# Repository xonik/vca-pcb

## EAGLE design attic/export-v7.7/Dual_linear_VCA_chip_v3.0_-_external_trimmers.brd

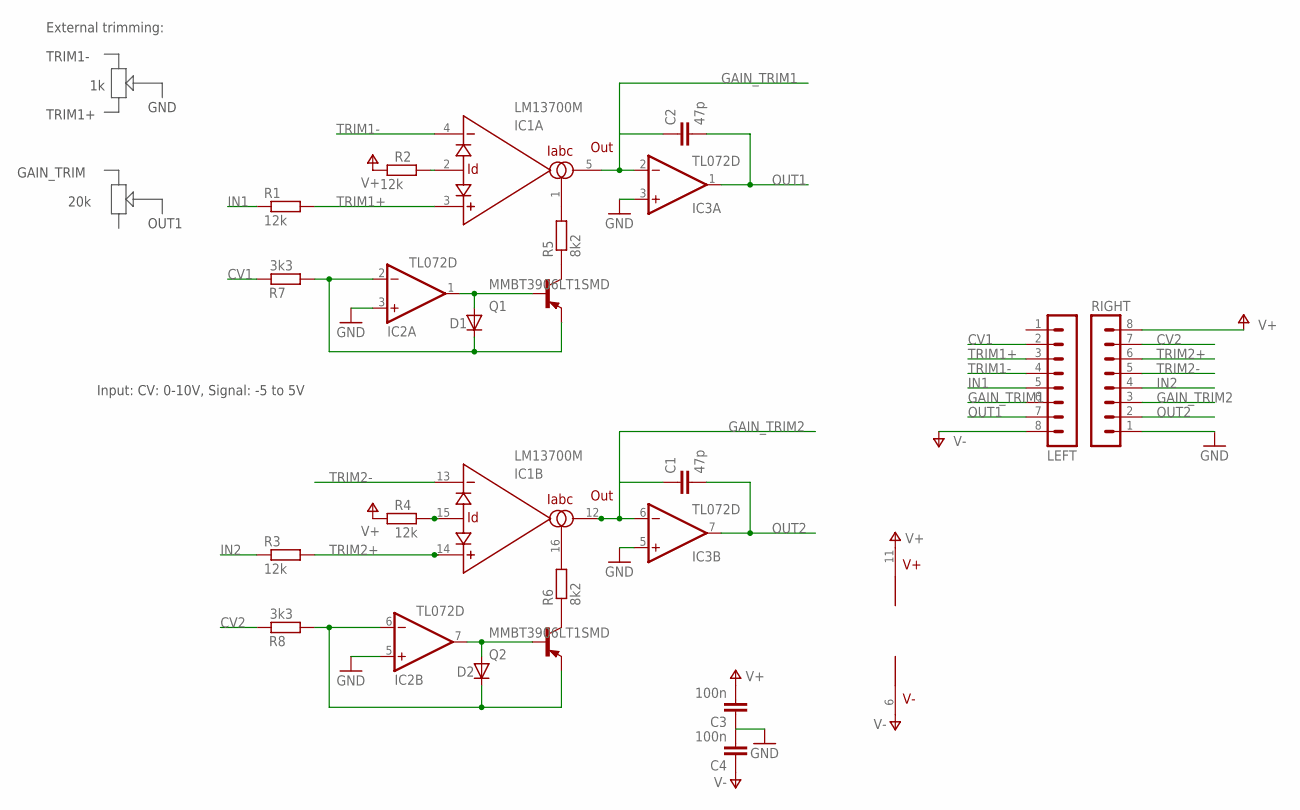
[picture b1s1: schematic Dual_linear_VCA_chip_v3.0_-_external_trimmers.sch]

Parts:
C1, C2: 47p; C0805
C3, C4: 100n; C0805
D1, D2: DIODE-SOD80C; SOD80C
IC1: LM13700M; SO16
IC2, IC3: TL072D; SO08
LEFT: MA08-1JC; MA08-1J
Q1, Q2: MMBT3906LT1SMD; SOT23-BEC
R1, R2, R3, R4: 12k; R0805
R5, R6: 8k2; R0805
R7, R8: 3k3; R0805
RIGHT: MA08-1JC; MA08-1J

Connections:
CV1: LEFT.2, R7.2
CV2: R8.2, RIGHT.7
GAIN_TRIM1: C2.1, IC1.5 (OUT), IC3.2 (-IN), LEFT.6
GAIN_TRIM2: C1.1, IC1.12 (OUT), IC3.6 (-IN), RIGHT.3
GND: C3.1, C4.2, IC2.3 (+IN), IC2.5 (+IN), IC3.3 (+IN), IC3.5 (+IN), RIGHT.1
IN1: LEFT.5, R1.1
IN2: R3.1, RIGHT.4
unnamed: Q1.C, R5.1
unnamed: Q2.C, R6.1
unnamed: D1.C, IC2.2 (-IN), Q1.E, R7.1
unnamed: IC1.1 (IABC), R5.2
unnamed: IC1.2 (ID), R2.2
unnamed: D2.A, IC2.7 (OUT), Q2.B
unnamed: D1.A, IC2.1 (OUT), Q1.B
unnamed: D2.C, IC2.6 (-IN), Q2.E, R8.1
unnamed: IC1.16 (IABC), R6.2
unnamed: IC1.15 (ID), R4.2
OUT1: C2.2, IC3.1 (OUT), LEFT.7
OUT2: C1.2, IC3.7 (OUT), RIGHT.2
TRIM1+: IC1.3 (+IN), LEFT.3, R1.2
TRIM1-: IC1.4 (-IN), LEFT.4
TRIM2+: IC1.14 (+IN), R3.2, RIGHT.6
TRIM2-: IC1.13 (-IN), RIGHT.5
V+: C3.2, IC1.11 (V+), IC2.8 (V+), IC3.8 (V+), R2.1, R4.1, RIGHT.8
V-: C4.1, IC1.6 (V-), IC2.4 (V-), IC3.4 (V-), LEFT.8

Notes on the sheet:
Input: CV: 0-10V, Signal: -5 to 5V
TRIM1-
TRIM1+
GND
External trimming:
GAIN_TRIM
OUT1
20k

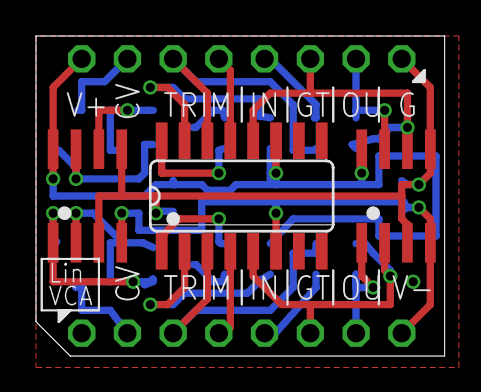
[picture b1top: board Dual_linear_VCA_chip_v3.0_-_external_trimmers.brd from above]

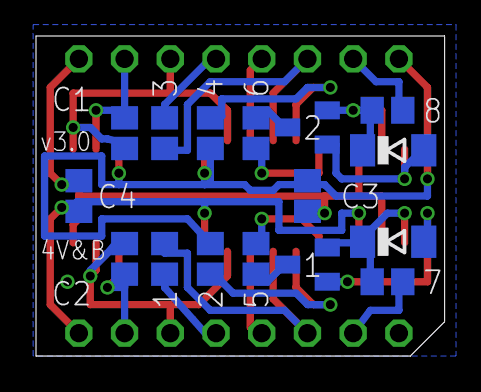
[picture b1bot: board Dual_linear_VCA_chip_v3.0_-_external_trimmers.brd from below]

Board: 2 copper layers, 22.7 x 17.8 mm, 21 parts (16 on the bottom side), 25 nets.

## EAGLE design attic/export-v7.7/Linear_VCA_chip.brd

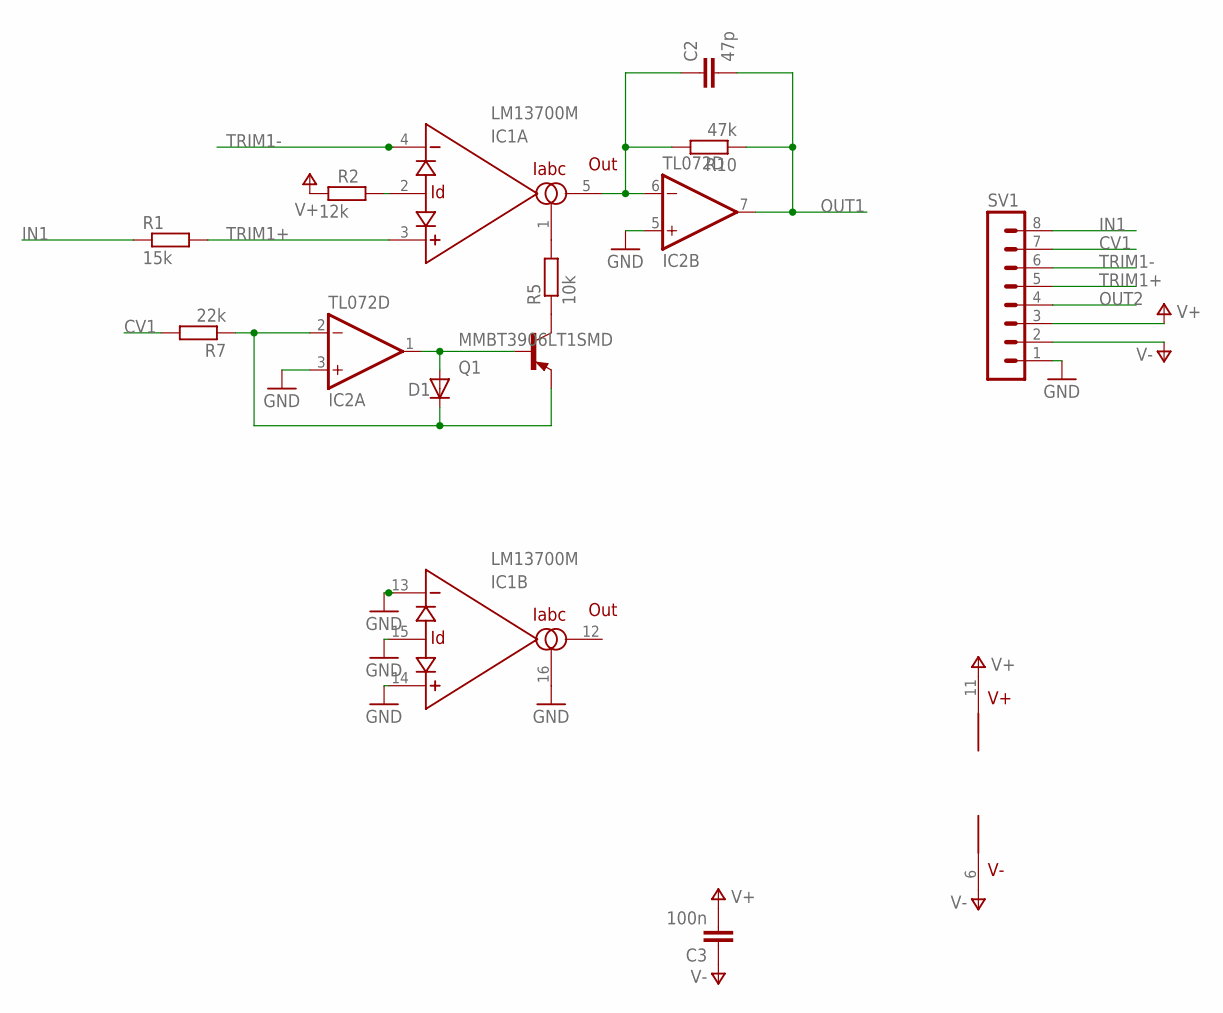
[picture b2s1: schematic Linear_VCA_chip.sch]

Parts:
C2: 47p; C0805
C3: 100n; C0805
D1: DIODE-SOD80C; SOD80C
IC1: LM13700M; SO16
IC2: TL072D; SO08
Q1: MMBT3906LT1SMD; SOT23-BEC
R1: 15k; R0805
R2: 12k; R0805
R5: 10k; R0805
R7: 22k; R0805
R10: 47k; R0805
SV1: MA08-1

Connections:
CV1: R7.2, SV1.7
GND: IC1.13 (-IN), IC1.14 (+IN), IC1.15 (ID), IC1.16 (IABC), IC2.3 (+IN), IC2.5 (+IN), SV1.1
IN1: R1.1, SV1.8
unnamed: Q1.C, R5.1
unnamed: D1.C, IC2.2 (-IN), Q1.E, R7.1
unnamed: IC1.1 (IABC), R5.2
unnamed: IC1.2 (ID), R2.2
unnamed: C2.1, IC1.5 (OUT), IC2.6 (-IN), R10.2
unnamed: D1.A, IC2.1 (OUT), Q1.B
OUT1: C2.2, IC2.7 (OUT), R10.1
OUT2: SV1.4
TRIM1+: IC1.3 (+IN), R1.2, SV1.5
TRIM1-: IC1.4 (-IN), SV1.6
V+: C3.2, IC1.11 (V+), IC2.8 (V+), R2.1, SV1.3
V-: C3.1, IC1.6 (V-), IC2.4 (V-), SV1.2

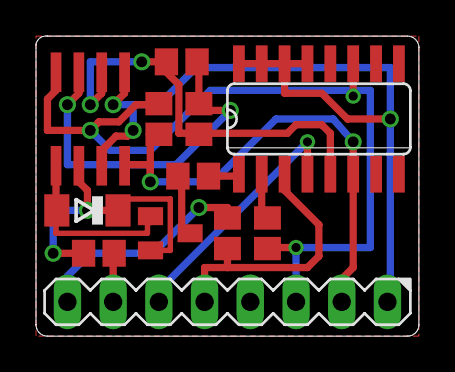
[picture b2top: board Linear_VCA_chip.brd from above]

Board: 2 copper layers, 21.3 x 16.7 mm, 12 parts (0 on the bottom side), 14 nets.

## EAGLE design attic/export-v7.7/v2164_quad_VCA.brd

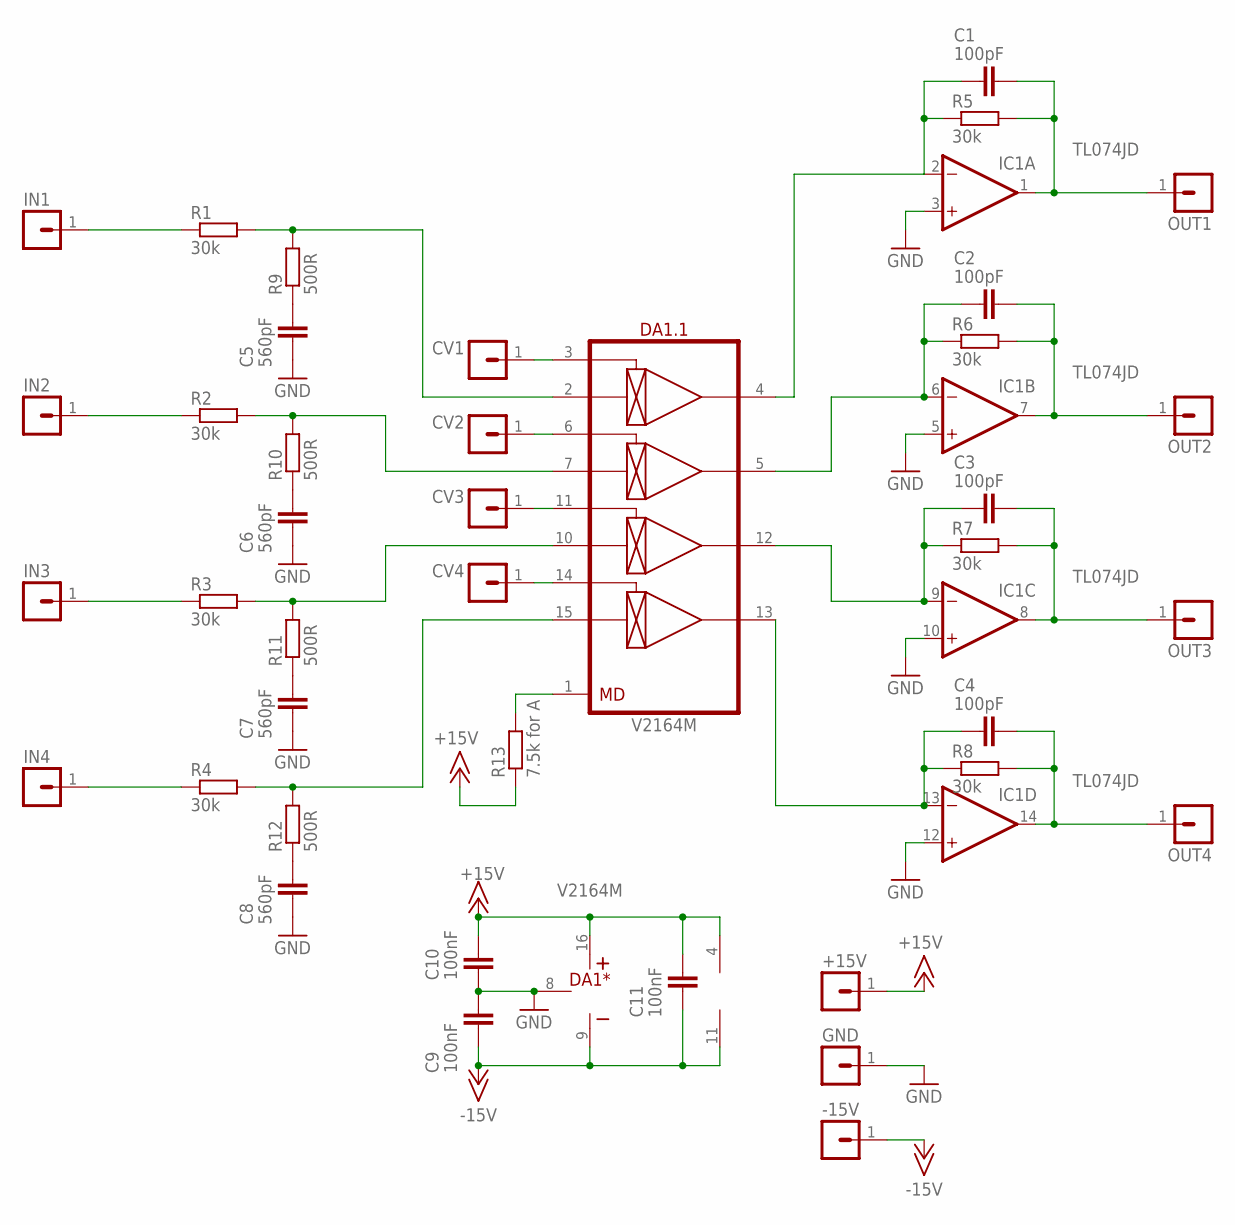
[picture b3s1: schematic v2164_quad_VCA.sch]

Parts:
+15V: MA01-1JN; MA01N-1J
-15V: MA01-1JN; MA01N-1J
C1, C2, C3, C4: 100pF; C0603
C5, C6, C7, C8: 560pF; C0603
C9, C10, C11: 100nF; C0603
CV1, CV2, CV3, CV4: MA01-1JN; MA01N-1J
DA1: V2164M; SO-16
GND: MA01-1JN; MA01N-1J
IC1: TL074JD; SO14J
IN1, IN2, IN3, IN4: MA01-1JN; MA01N-1J
OUT1, OUT2, OUT3, OUT4: MA01-1JN; MA01N-1J
R1, R2, R3, R4, R5, R6, R7, R8: 30k; R0603
R9, R10, R11, R12: 500R; R0603
R13: 7.5k for A; R0603

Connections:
+15V: +15V.1, C10.2, C11.2, DA1.16 (V+), IC1.4 (V+), R13.1
-15V: -15V.1, C9.1, C11.1, DA1.9 (V-), IC1.11 (V-)
CV1: CV1.1, DA1.3 (CV1)
CV2: CV2.1, DA1.6 (CV2)
CV3: CV3.1, DA1.11 (CV3)
CV4: CV4.1, DA1.14 (CV4)
GND: C5.1, C6.1, C7.1, C8.1, C9.2, C10.1, DA1.8 (GND), GND.1, IC1.3 (+IN), IC1.5 (+IN), IC1.10 (+IN), IC1.12 (+IN)
IN1: IN1.1, R1.1
IN2: IN2.1, R2.1
IN3: IN3.1, R3.1
IN4: IN4.1, R4.1
unnamed: C4.1, DA1.13 (OUT4), IC1.13 (-IN), R8.1
unnamed: DA1.1 (MD), R13.2
unnamed: C3.1, DA1.12 (OUT3), IC1.9 (-IN), R7.1
unnamed: C2.1, DA1.5 (OUT2), IC1.6 (-IN), R6.1
unnamed: C1.1, DA1.4 (OUT1), IC1.2 (-IN), R5.1
unnamed: C5.2, R9.1
unnamed: C6.2, R10.1
unnamed: C7.2, R11.1
unnamed: C8.2, R12.1
unnamed: DA1.2 (IN1), R1.2, R9.2
unnamed: DA1.7 (IN2), R2.2, R10.2
unnamed: DA1.10 (IN3), R3.2, R11.2
unnamed: DA1.15 (IN4), R4.2, R12.2
OUT1: C1.2, IC1.1 (OUT), OUT1.1, R5.2
OUT2: C2.2, IC1.7 (OUT), OUT2.1, R6.2
OUT3: C3.2, IC1.8 (OUT), OUT3.1, R7.2
OUT4: C4.2, IC1.14 (OUT), OUT4.1, R8.2

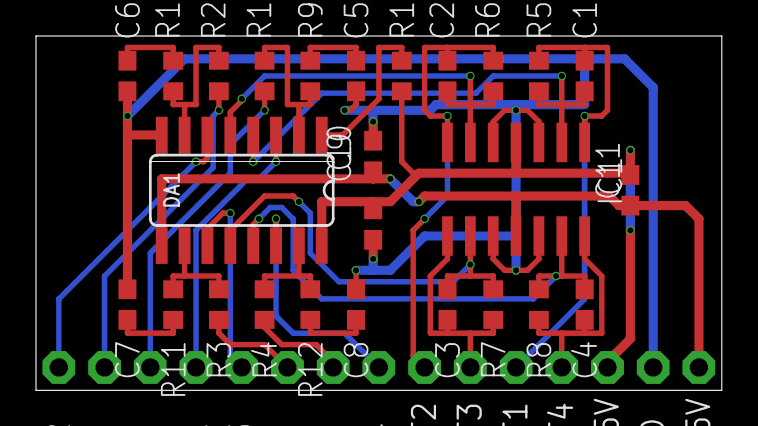
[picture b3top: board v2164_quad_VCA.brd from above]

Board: 2 copper layers, 38.1 x 19.7 mm, 41 parts (0 on the bottom side), 28 nets.

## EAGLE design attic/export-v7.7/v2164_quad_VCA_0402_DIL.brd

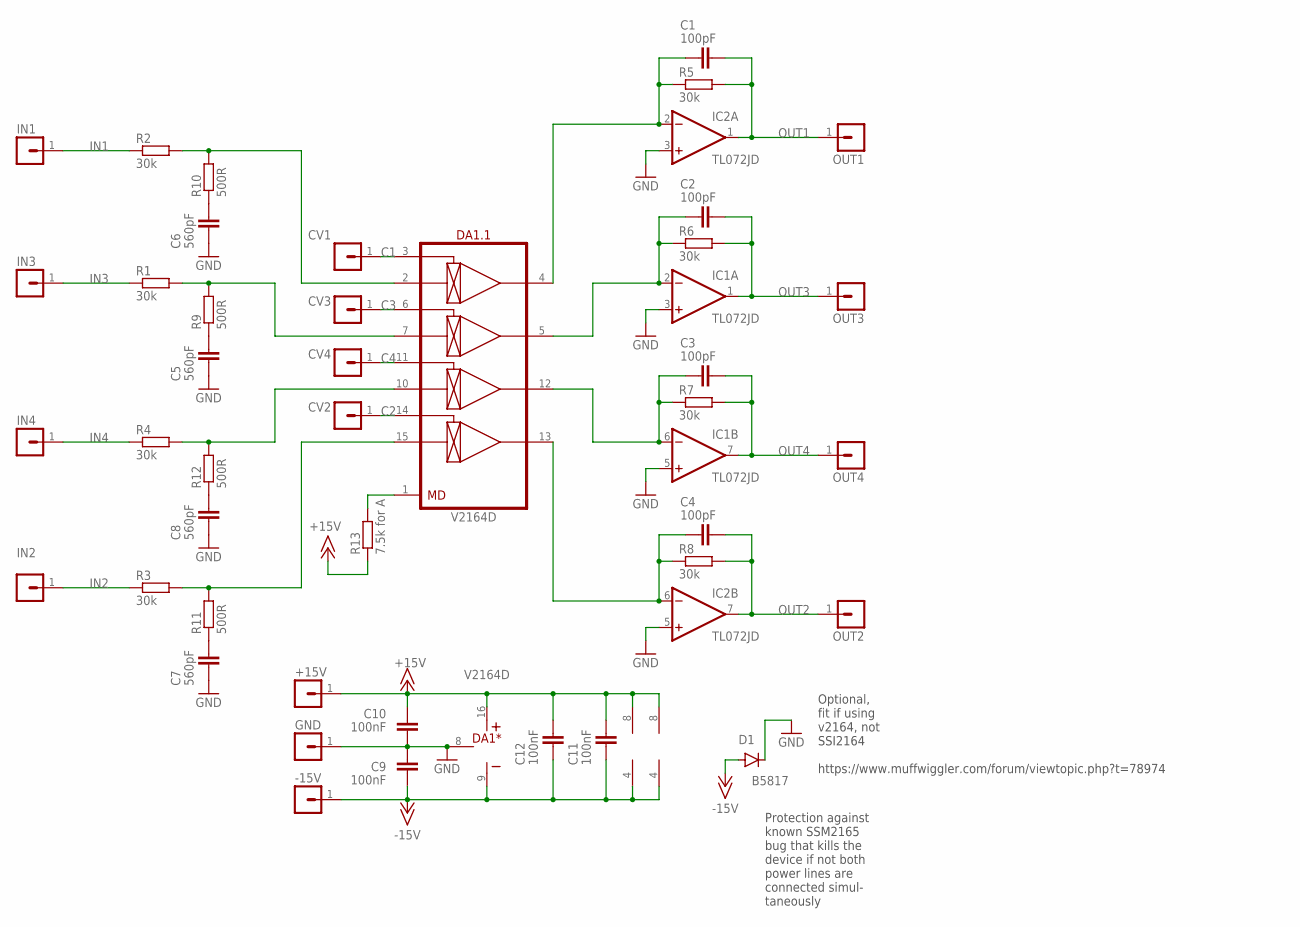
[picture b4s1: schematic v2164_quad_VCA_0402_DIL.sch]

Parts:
+15V: MA01-1JP; SIP-PIN01-1J
-15V: MA01-1JP; SIP-PIN01-1J
C1, C2, C3, C4: 100pF; C0402
C5, C6, C7, C8: 560pF; C0603
C9, C10, C11, C12: 100nF; C0402
CV1, CV2, CV3, CV4: MA01-1JP; SIP-PIN01-1J
D1: B5817; SOD323-R
DA1: V2164D; DIP-16
GND: MA01-1JP; SIP-PIN01-1J
IC1, IC2: TL072JD; SO08J
IN1, IN2, IN3, IN4: MA01-1JP; SIP-PIN01-1J
OUT1, OUT2, OUT3, OUT4: MA01-1JP; SIP-PIN01-1J
R1, R2, R3, R4, R5, R6, R7, R8: 30k; R0402
R9, R10, R11, R12: 500R; R0402
R13: 7.5k for A; R0402

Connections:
+15V: +15V.1, C10.2, C11.2, C12.2, DA1.16 (V+), IC1.8 (V+), IC2.8 (V+), R13.1
-15V: -15V.1, C9.1, C11.1, C12.1, D1.A, DA1.9 (V-), IC1.4 (V-), IC2.4 (V-)
C1: CV1.1, DA1.3 (CV1)
C2: CV2.1, DA1.14 (CV4)
C3: CV3.1, DA1.6 (CV2)
C4: CV4.1, DA1.11 (CV3)
GND: C5.1, C6.1, C7.1, C8.1, C9.2, C10.1, D1.C, DA1.8 (GND), GND.1, IC1.3 (+IN), IC1.5 (+IN), IC2.3 (+IN), IC2.5 (+IN)
IN1: IN1.1, R2.1
IN2: IN2.1, R3.1
IN3: IN3.1, R1.1
IN4: IN4.1, R4.1
unnamed: C4.1, DA1.13 (OUT4), IC2.6 (-IN), R8.1
unnamed: DA1.1 (MD), R13.2
unnamed: C3.1, DA1.12 (OUT3), IC1.6 (-IN), R7.1
unnamed: C2.1, DA1.5 (OUT2), IC1.2 (-IN), R6.1
unnamed: C1.1, DA1.4 (OUT1), IC2.2 (-IN), R5.1
unnamed: C5.2, R9.1
unnamed: C6.2, R10.1
unnamed: C7.2, R11.1
unnamed: C8.2, R12.1
unnamed: DA1.7 (IN2), R1.2, R9.2
unnamed: DA1.2 (IN1), R2.2, R10.2
unnamed: DA1.15 (IN4), R3.2, R11.2
unnamed: DA1.10 (IN3), R4.2, R12.2
OUT1: C1.2, IC2.1 (OUT), OUT1.1, R5.2
OUT2: C4.2, IC2.7 (OUT), OUT2.1, R8.2
OUT3: C2.2, IC1.1 (OUT), OUT3.1, R6.2
OUT4: C3.2, IC1.7 (OUT), OUT4.1, R7.2

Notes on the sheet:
Optional, fit if using v2164, not SSI2164 https://www.muffwiggler.com/forum/viewtopic.php?t=78974
Protection against known SSM2165 bug that kills the device if not both power lines are connected simul- taneously

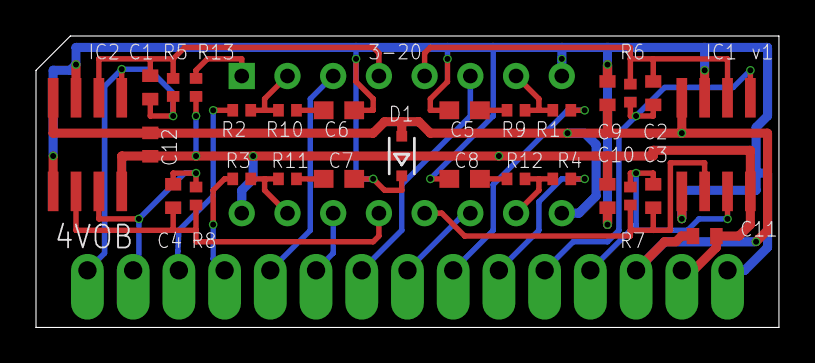
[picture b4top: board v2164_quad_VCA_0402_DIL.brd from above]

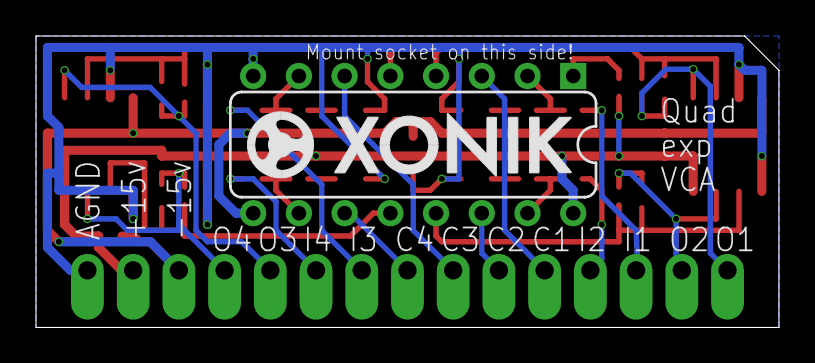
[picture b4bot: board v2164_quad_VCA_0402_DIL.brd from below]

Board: 2 copper layers, 41.3 x 16.2 mm, 45 parts (2 on the bottom side), 28 nets.

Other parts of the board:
U$1: XONIK_LOGO_18

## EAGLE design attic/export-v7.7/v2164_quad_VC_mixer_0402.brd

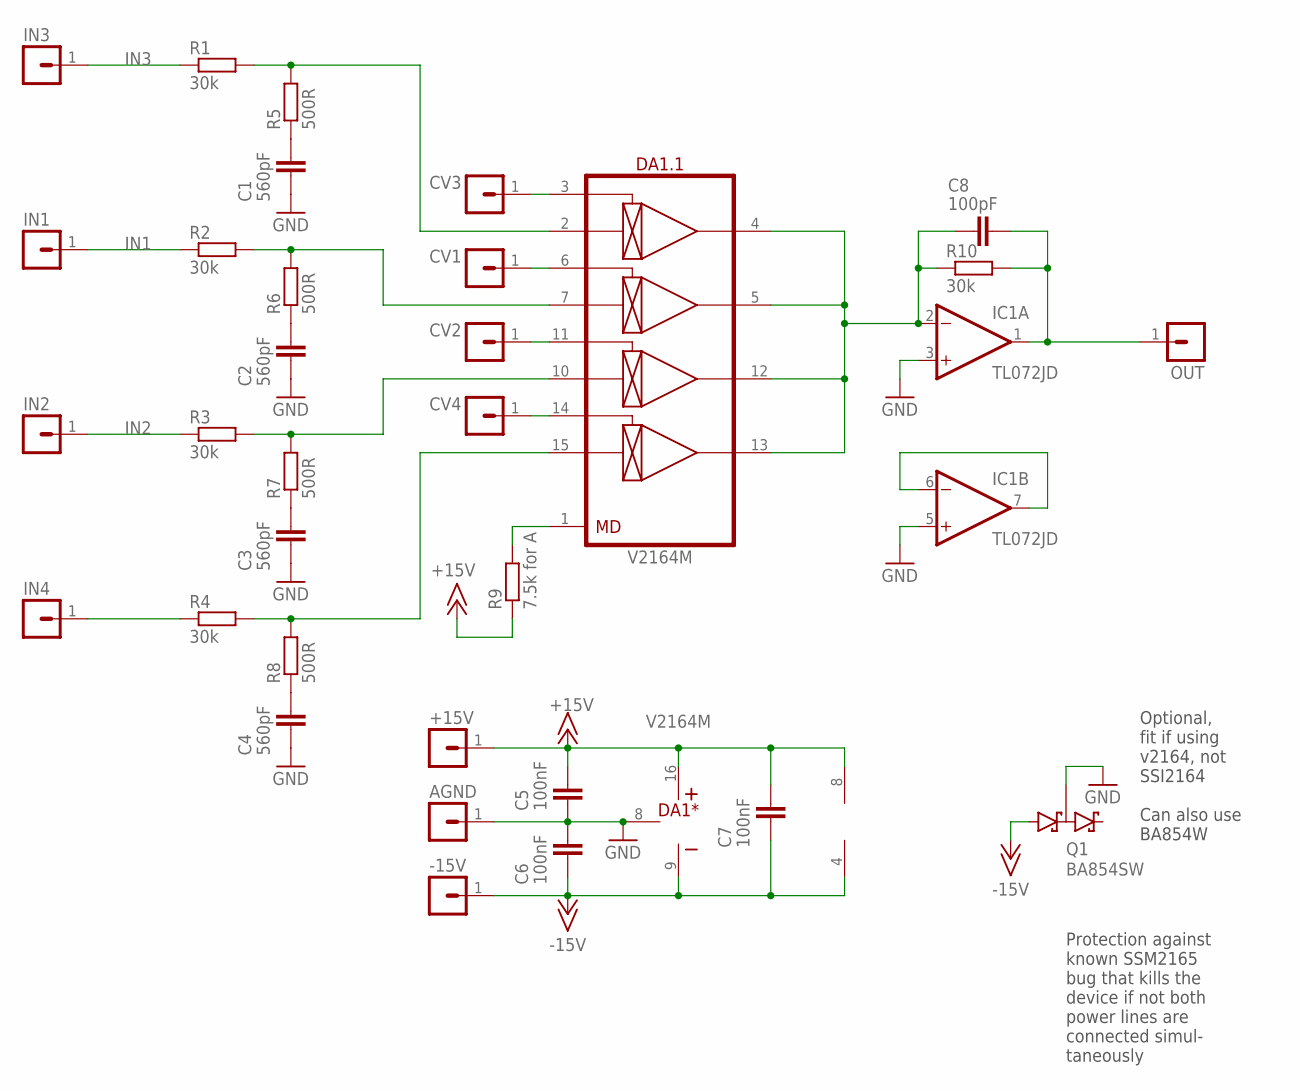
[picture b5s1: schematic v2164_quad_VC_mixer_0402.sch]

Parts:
+15V: MA01-1JN; MA01N-1J
-15V: MA01-1JN; MA01N-1J
AGND: MA01-1JN; MA01N-1J
C1, C2, C3, C4: 560pF; C0603
C5, C6, C7: 100nF; C0402
C8: 100pF; C0402
CV1, CV2, CV3, CV4: MA01-1JN; MA01N-1J
DA1: V2164M; SO-16
IC1: TL072JD; SO08J
IN1, IN2, IN3, IN4: MA01-1JN; MA01N-1J
OUT: MA01-1JN; MA01N-1J
Q1: BA854SW; SOT23-3J
R1, R2, R3, R4, R10: 30k; R0402
R5, R6, R7, R8: 500R; R0402
R9: 7.5k for A; R0402

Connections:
+15V: +15V.1, C5.2, C7.2, DA1.16 (V+), IC1.8 (V+), R9.1
-15V: -15V.1, C6.1, C7.1, DA1.9 (V-), IC1.4 (V-), Q1.1 (A1)
CV1: CV1.1, DA1.6 (CV2)
CV2: CV2.1, DA1.11 (CV3)
CV4: CV4.1, DA1.14 (CV4)
CV5: CV3.1, DA1.3 (CV1)
GND: AGND.1, C1.1, C2.1, C3.1, C4.1, C5.1, C6.2, DA1.8 (GND), IC1.3 (+IN), IC1.5 (+IN), Q1.3 (K1A2)
IN1: IN1.1, R2.1
IN2: IN2.1, R3.1
IN3: IN3.1, R1.1
IN4: IN4.1, R4.1
unnamed: IC1.6 (-IN), IC1.7 (OUT)
unnamed: DA1.1 (MD), R9.2
unnamed: C8.1, DA1.4 (OUT1), DA1.5 (OUT2), DA1.12 (OUT3), DA1.13 (OUT4), IC1.2 (-IN), R10.1
unnamed: C1.2, R5.1
unnamed: C2.2, R6.1
unnamed: C3.2, R7.1
unnamed: C4.2, R8.1
unnamed: DA1.2 (IN1), R1.2, R5.2
unnamed: DA1.7 (IN2), R2.2, R6.2
unnamed: DA1.10 (IN3), R3.2, R7.2
unnamed: DA1.15 (IN4), R4.2, R8.2
OUT: C8.2, IC1.1 (OUT), OUT.1, R10.2

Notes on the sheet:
Optional, fit if using v2164, not SSI2164 Can also use BA854W
Protection against known SSM2165 bug that kills the device if not both power lines are connected simul- taneously

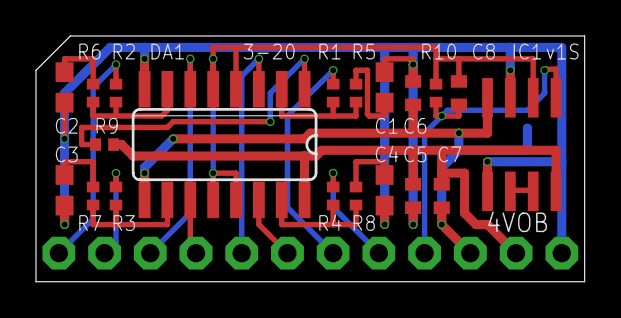
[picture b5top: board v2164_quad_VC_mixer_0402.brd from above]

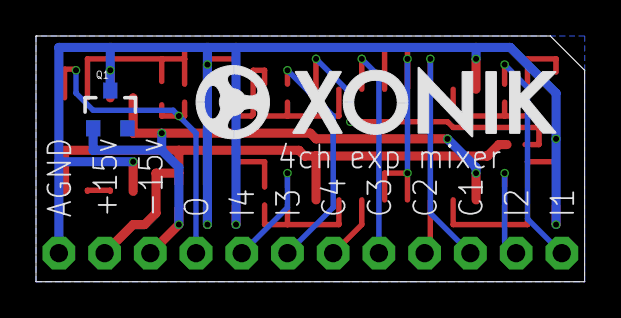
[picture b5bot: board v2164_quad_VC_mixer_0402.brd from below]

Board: 2 copper layers, 30.5 x 13.7 mm, 34 parts (2 on the bottom side), 23 nets.

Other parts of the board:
U$1: XONIK_LOGO_20
